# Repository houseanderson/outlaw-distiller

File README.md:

### Welcome

If you're coming here from YouTube (@TheOutlawPhilosopher) you likely already have an idea of what this project is about.

Otherwise, you may be dissapointed that this has nothing to do with alochol distillation...  sorry.

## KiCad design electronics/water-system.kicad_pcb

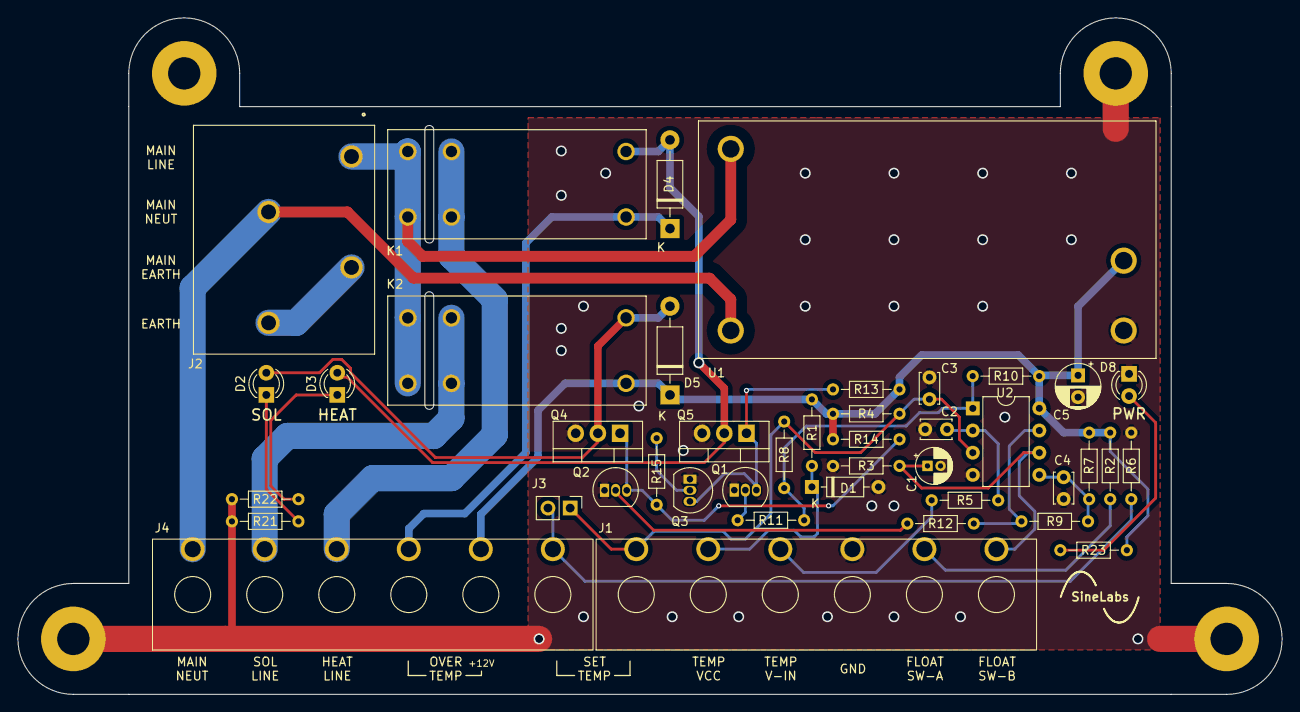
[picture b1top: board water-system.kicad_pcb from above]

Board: 2 copper layers, 144.8 x 77.5 mm, 46 parts (0 on the bottom side), 28 nets.

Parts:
C1: 10u; CP_Radial_D4.0mm_P1.50mm
C2: 10n; C_Disc_D3.4mm_W2.1mm_P2.50mm
C3, C4: 1n; C_Disc_D3.4mm_W2.1mm_P2.50mm
C5: 100u; CP_Radial_D5.0mm_P2.50mm
D1: 3.3VZ; D_DO-35_SOD27_P7.62mm_Horizontal
D2, D3: LED_Filled; LED_D3.0mm_Clear
D4, D5: 1N5819; D_DO-41_SOD81_P10.16mm_Horizontal
D8: LED_Filled; LED_D3.0mm
H1, H2, H3, H4: MountingHole_Pad; MountingHole_3.7mm_Pad
J1, J4: Screw_Terminal_01x06; OSTYK42106030
J2: Screw_Terminal_01x04; PHOENIX_1017516
J3: Conn_01x02_Male; PinHeader_1x02_P2.54mm_Vertical
K1, K2: G2RL-1A-E
Q1, Q2, Q3: 2N3904; TO-92_Inline
Q4, Q5: NDF05N50Z; TO-220-3_Vertical
R1: 4.7k; R_Axial_DIN0204_L3.6mm_D1.6mm_P7.62mm_Horizontal
R2, R3: 220k; R_Axial_DIN0204_L3.6mm_D1.6mm_P7.62mm_Horizontal
R4, R14, R15: 10k; R_Axial_DIN0204_L3.6mm_D1.6mm_P7.62mm_Horizontal
R5: 56k; R_Axial_DIN0204_L3.6mm_D1.6mm_P7.62mm_Horizontal
R6: 470; R_Axial_DIN0204_L3.6mm_D1.6mm_P7.62mm_Horizontal
R7: 5k; R_Axial_DIN0204_L3.6mm_D1.6mm_P7.62mm_Horizontal
R8: 330K; R_Axial_DIN0204_L3.6mm_D1.6mm_P7.62mm_Horizontal
R9, R11, R12, R21, R22, R23: 1k; R_Axial_DIN0204_L3.6mm_D1.6mm_P7.62mm_Horizontal
R10, R13: 33k; R_Axial_DIN0204_L3.6mm_D1.6mm_P7.62mm_Horizontal
U1: MPM-20-12; MPM-20
U2: LM393; DIP-8_W7.62mm

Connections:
+12V: C5.1, D5.1 (K), J4.5, K2.8, R1.2, R2.2, R4.1, R7.2, R10.2, R13.2, R14.2, R23.2, U1.4 (+Vo), U2.8 (V+)
/CFS_P1: C4.2, R7.1, R9.2, U2.5 (+)
/CFS_P2: C1.1, J1.6, R3.1, U2.6 (-)
/CFS_P3: R9.1, R12.2, U2.7
/COIL1_A: D4.1 (K), J4.4, K1.8
/COIL1_B: D3.2 (A), D4.2 (A), K1.1, Q5.2 (D)
/COIL2_B: D2.2 (A), D5.2 (A), K2.1, Q4.2 (D)
/CT_P1: C3.1, J1.1, J3.1, R4.2, R8.2, U2.3 (+)
/CT_P2: C2.1, R5.1, U2.2 (-)
/CT_P3: R8.1, R10.1, R11.2, U2.1
/FLOAT_SW_A: J1.5, R2.1
/HEAT_LINE: J4.3, K1.3, K1.6
/SOL_LINE: J4.2, K2.3, K2.6
/TP_B: J3.2, J4.6, R6.2
/V_TEMP: J1.3, R5.2
Earth: J2.3, J2.4
GND: C1.2, C2.2, C3.2, C4.1, C5.2, D1.2 (A), D8.1 (K), H2.1, H3.1, H4.1, J1.4, Q1.1 (E), Q2.1 (E), Q3.1 (E), Q4.3 (S), Q5.3 (S), R3.2, R6.1, R21.1, R22.2, U1.3 (-Vo), U2.4 (V-)
LINE: J2.1, K1.4, K1.5, K2.4, K2.5, U1.1 (AC/L)
NEUT: J2.2, J4.1, U1.2 (AC/N)
unnamed: D1.1 (K), J1.2, R1.1
unnamed: D2.1 (K), R21.2
unnamed: D3.1 (K), R22.1
unnamed: D8.2 (A), R23.1
unnamed: Q1.2 (B), R11.1
unnamed: Q1.3 (C), Q3.3 (C), Q5.1 (G), R13.1
unnamed: Q2.2 (B), R12.1
unnamed: Q2.3 (C), Q4.1 (G), R14.1, R15.2
unnamed: Q3.2 (B), R15.1

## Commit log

2024-05-05 Initial Commit - Corresponds to YouTube Video Release @TheOutlawPhilosopher S01E10
